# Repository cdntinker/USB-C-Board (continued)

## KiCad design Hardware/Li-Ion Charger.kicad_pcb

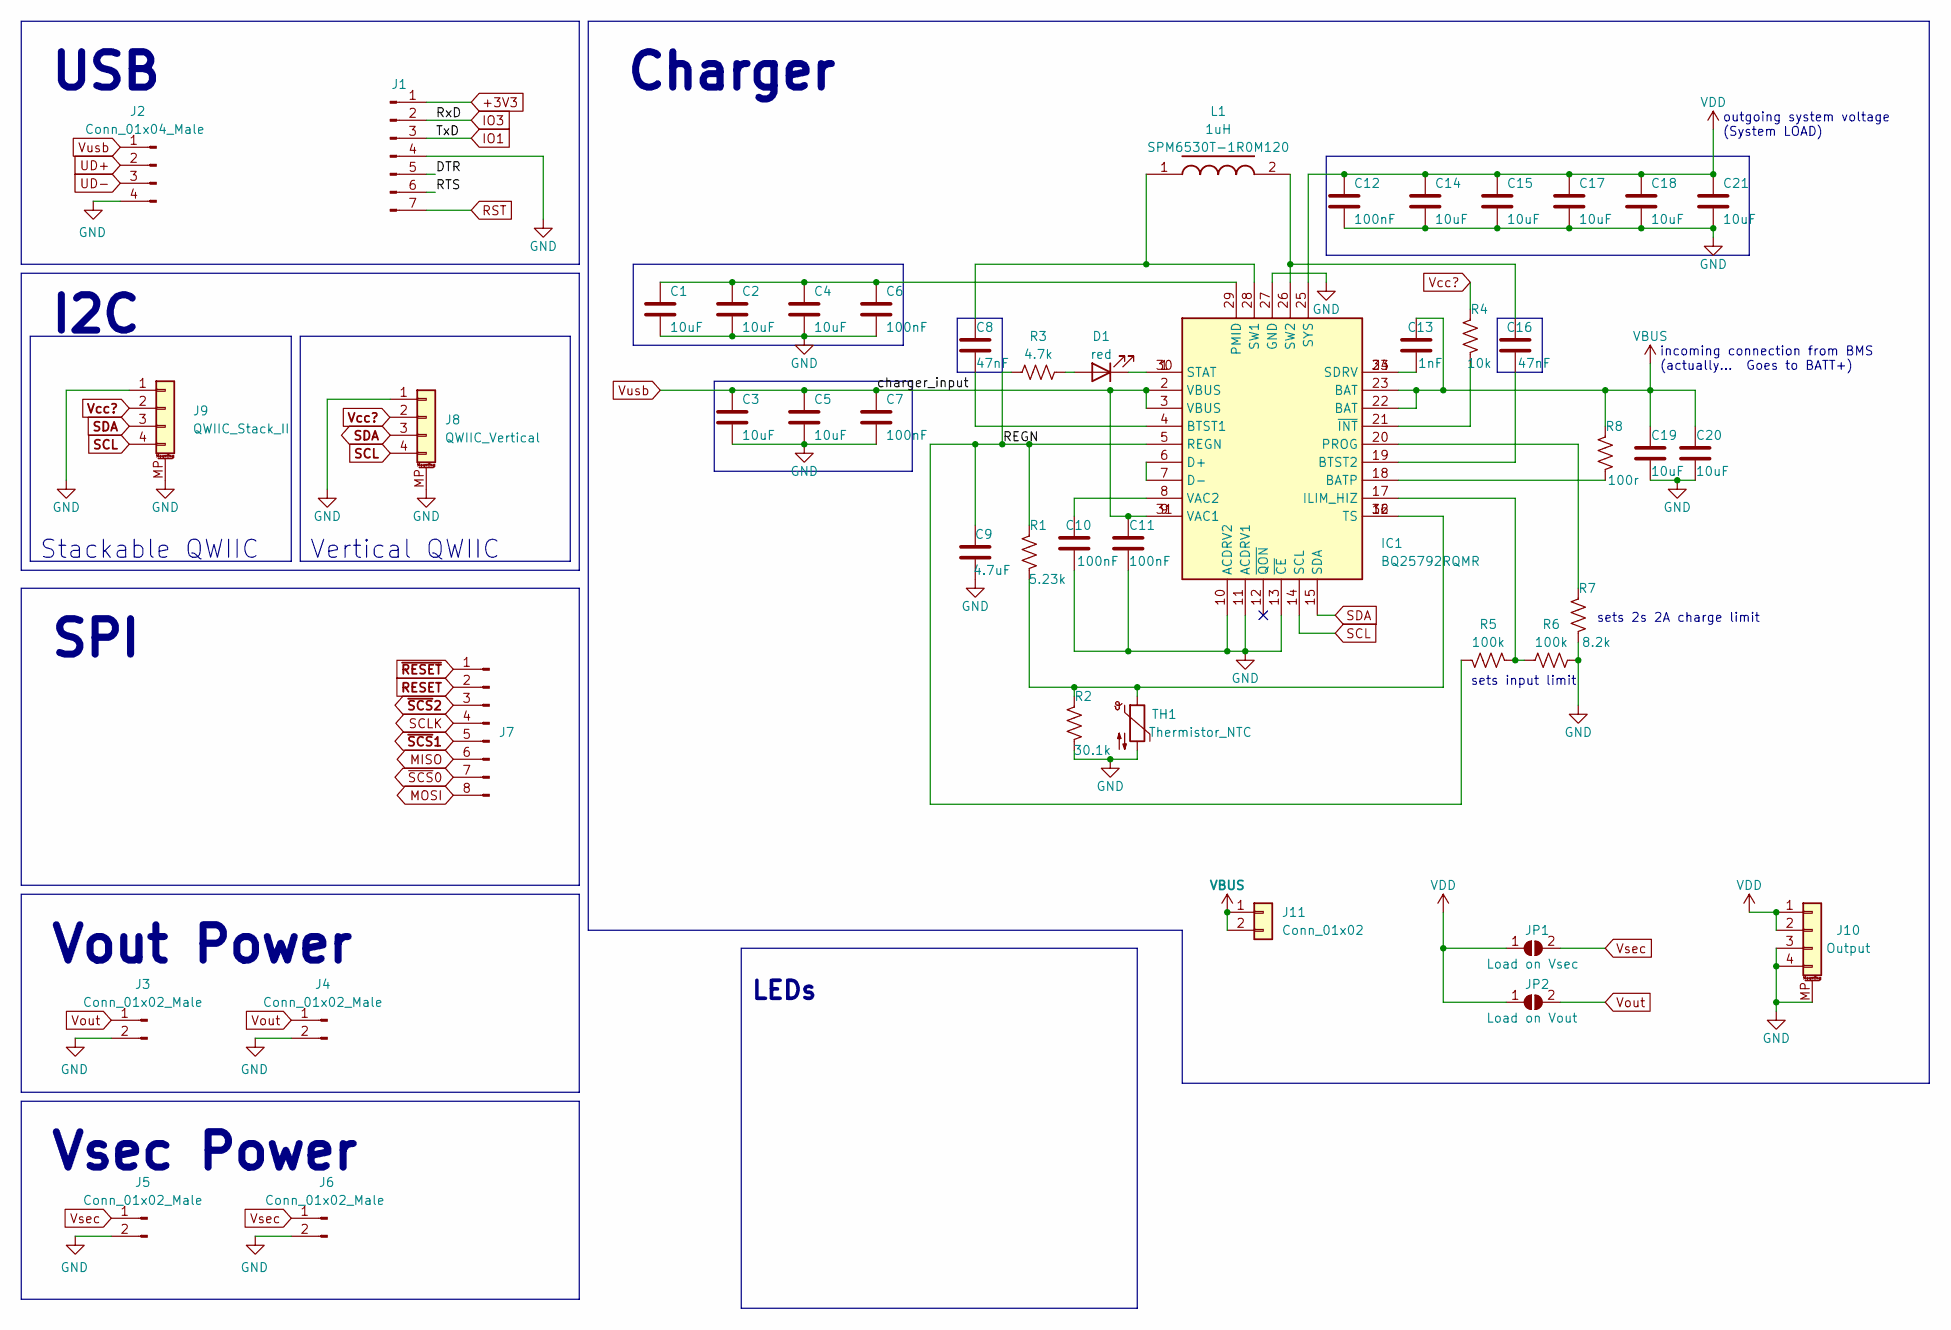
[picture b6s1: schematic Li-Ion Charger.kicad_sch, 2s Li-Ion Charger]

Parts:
C1, C2, C3, C4, C5, C14, C15, C17, C18, C19, C20, C21: 10uF; R_0603_1608Metric; LCSC C194427
C6, C7, C10, C11, C12: 100nF; R_0603_1608Metric
C8, C16: 47nF; R_0603_1608Metric; LCSC C469624
C9: 4.7uF; R_0603_1608Metric; LCSC C152930
C13: 1nF; R_0603_1608Metric
D1: red; LED_0603_1608Metric; LCSC C72038
IC1: BQ25792RQMR; Mouser 595-BQ25792RQMR
J1: Conn_01x07_Male; Board_Stacker_7
J2: Conn_01x04_Male; Board_Stacker_4; LCSC C2938401 + C2881513
J3, J4, J5, J6: Conn_01x02_Male; Board_Stacker_2; LCSC C2938400 + C2881511
J7: Conn_01x08_Male; PinHeader_2x04_P1.27mm_Vertical; LCSC C2881786 + C2684732
J8: QWIIC_Vertical; LCSC C145961
J9: QWIIC_Stack_II; LCSC C145956 + C2938401 + C2881513
J10: Output; JST_GH_SM04B-GHS-TB_1x04-1MP_P1.25mm_Horizontal; LCSC C225113
J11: Conn_01x02; PinSocket_1x02_P1.27mm_Vertical
JP1: Load on Vsec; SolderJumper-2_P_Open_Rounded_skinny
JP2: Load on Vout; SolderJumper-2_P_Open_Rounded_skinny
L1: 1uH; SPM6530_TDK; Mouser 810-SPM6530T-1R0M120
R1: 5.23k; R_0603_1608Metric
R2: 30.1k; R_0603_1608Metric; LCSC C2960871
R3: 4.7k; R_0603_1608Metric
R4: 10k; R_0603_1608Metric; LCSC C98220
R5, R6: 100k; R_0603_1608Metric
R7: 8.2k; R_0603_1608Metric
R8: 100r; R_0603_1608Metric
TH1: Thermistor_NTC; R_0603_1608Metric; LCSC C13564

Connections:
/REGN: C9.2, IC1.5 (REGN), R1.1, R3.1, R5.2
GND: C1.1, C2.1, C3.1, C4.1, C5.1, C6.1, C7.1, C9.1, C10.1, C11.1, C12.1, C14.1, C15.1, C17.1, C18.1, C19.1, C20.1, C21.1, IC1.10 (ACDRV2), IC1.11 (ACDRV1), IC1.13 (~CE), IC1.27 (GND), J1.4, J2.4, J3.2, J4.2, J5.2, J6.2, J8.1, J8.MP (MountPin), J9.1, J9.MP (MountPin), J10.3, J10.4, J10.MP (MountPin), R2.2, R6.2, R7.2, TH1.2
MISO: J7.6
MOSI: J7.8
unnamed: C1.2, C2.2, C4.2, C6.2, IC1.29 (PMID)
unnamed: C8.1, IC1.28 (SW1), L1.1
unnamed: C8.2, IC1.4 (BTST1)
unnamed: C10.2, IC1.8 (VAC2)
unnamed: C13.1, IC1.24 (SDRV), IC1.33 (SDRV)
unnamed: C16.1, IC1.19 (BTST2)
unnamed: C16.2, IC1.26 (SW2), L1.2
unnamed: D1.1 (K), IC1.1 (STAT), IC1.30 (STAT)
unnamed: D1.2 (A), R3.2
unnamed: IC1.6 (D+), IC1.7 (D-)
unnamed: IC1.16 (TS), IC1.32 (TS), R1.2, R2.1, TH1.1
unnamed: IC1.17 (ILIM_HIZ), R5.1, R6.1
unnamed: IC1.18 (BATP), R8.2
unnamed: IC1.20 (PROG), R7.1
unnamed: IC1.21 (~INT), R4.1
RESET: J7.2
SCL: IC1.14 (SCL), J8.4, J9.4
SCLK: J7.4
SDA: IC1.15 (SDA), J8.3, J9.3
UD+: J2.2
UD-: J2.3
VBUS: C13.2, C19.2, C20.2, IC1.22 (BAT), IC1.23 (BAT), J11.1, J11.2, R8.1
VDD: C12.2, C14.2, C15.2, C17.2, C18.2, C21.2, IC1.25 (SYS), J10.1, J10.2, JP1.1 (A), JP2.1 (A)
Vcc?: J8.2, J9.2, R4.2
Vout: J3.1, J4.1, JP2.2 (B)
Vsec: J5.1, J6.1, JP1.2 (B)
Vusb: C3.2, C5.2, C7.2, C11.2, IC1.2 (VBUS), IC1.3 (VBUS), IC1.9 (VAC1), IC1.31 (VAC1), J2.1
~RESET: J7.1
~SCS0: J7.7
~SCS1: J7.5
~SCS2: J7.3

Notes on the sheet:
Vout Power
I2C
Stackable QWIIC
incoming connection from BMS (actually... Goes to BATT+)
sets 2s 2A charge limit
SPI
Vsec Power
USB
outgoing system voltage (System LOAD)
sets input limit
Vertical QWIIC
Charger
LEDs

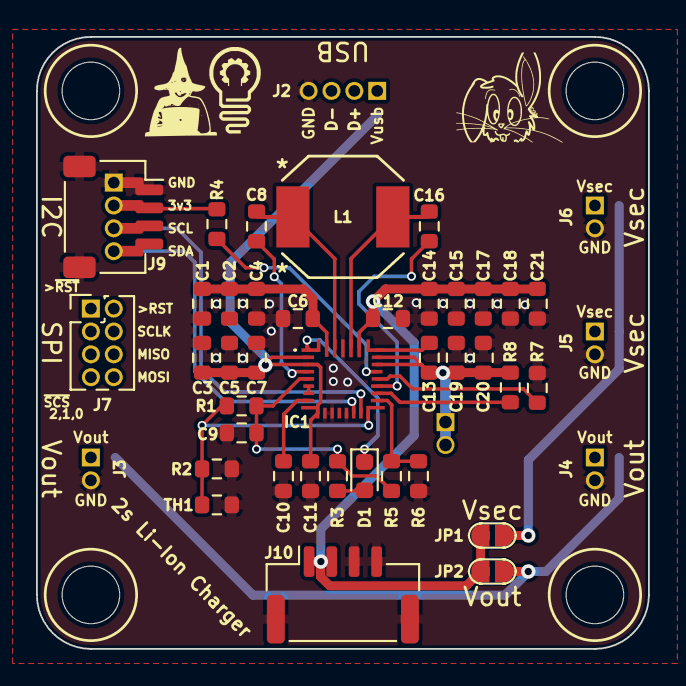
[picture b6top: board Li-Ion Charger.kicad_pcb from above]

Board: 2 copper layers, 34.0 x 34.0 mm, 44 parts (1 on the bottom side), 25 nets.

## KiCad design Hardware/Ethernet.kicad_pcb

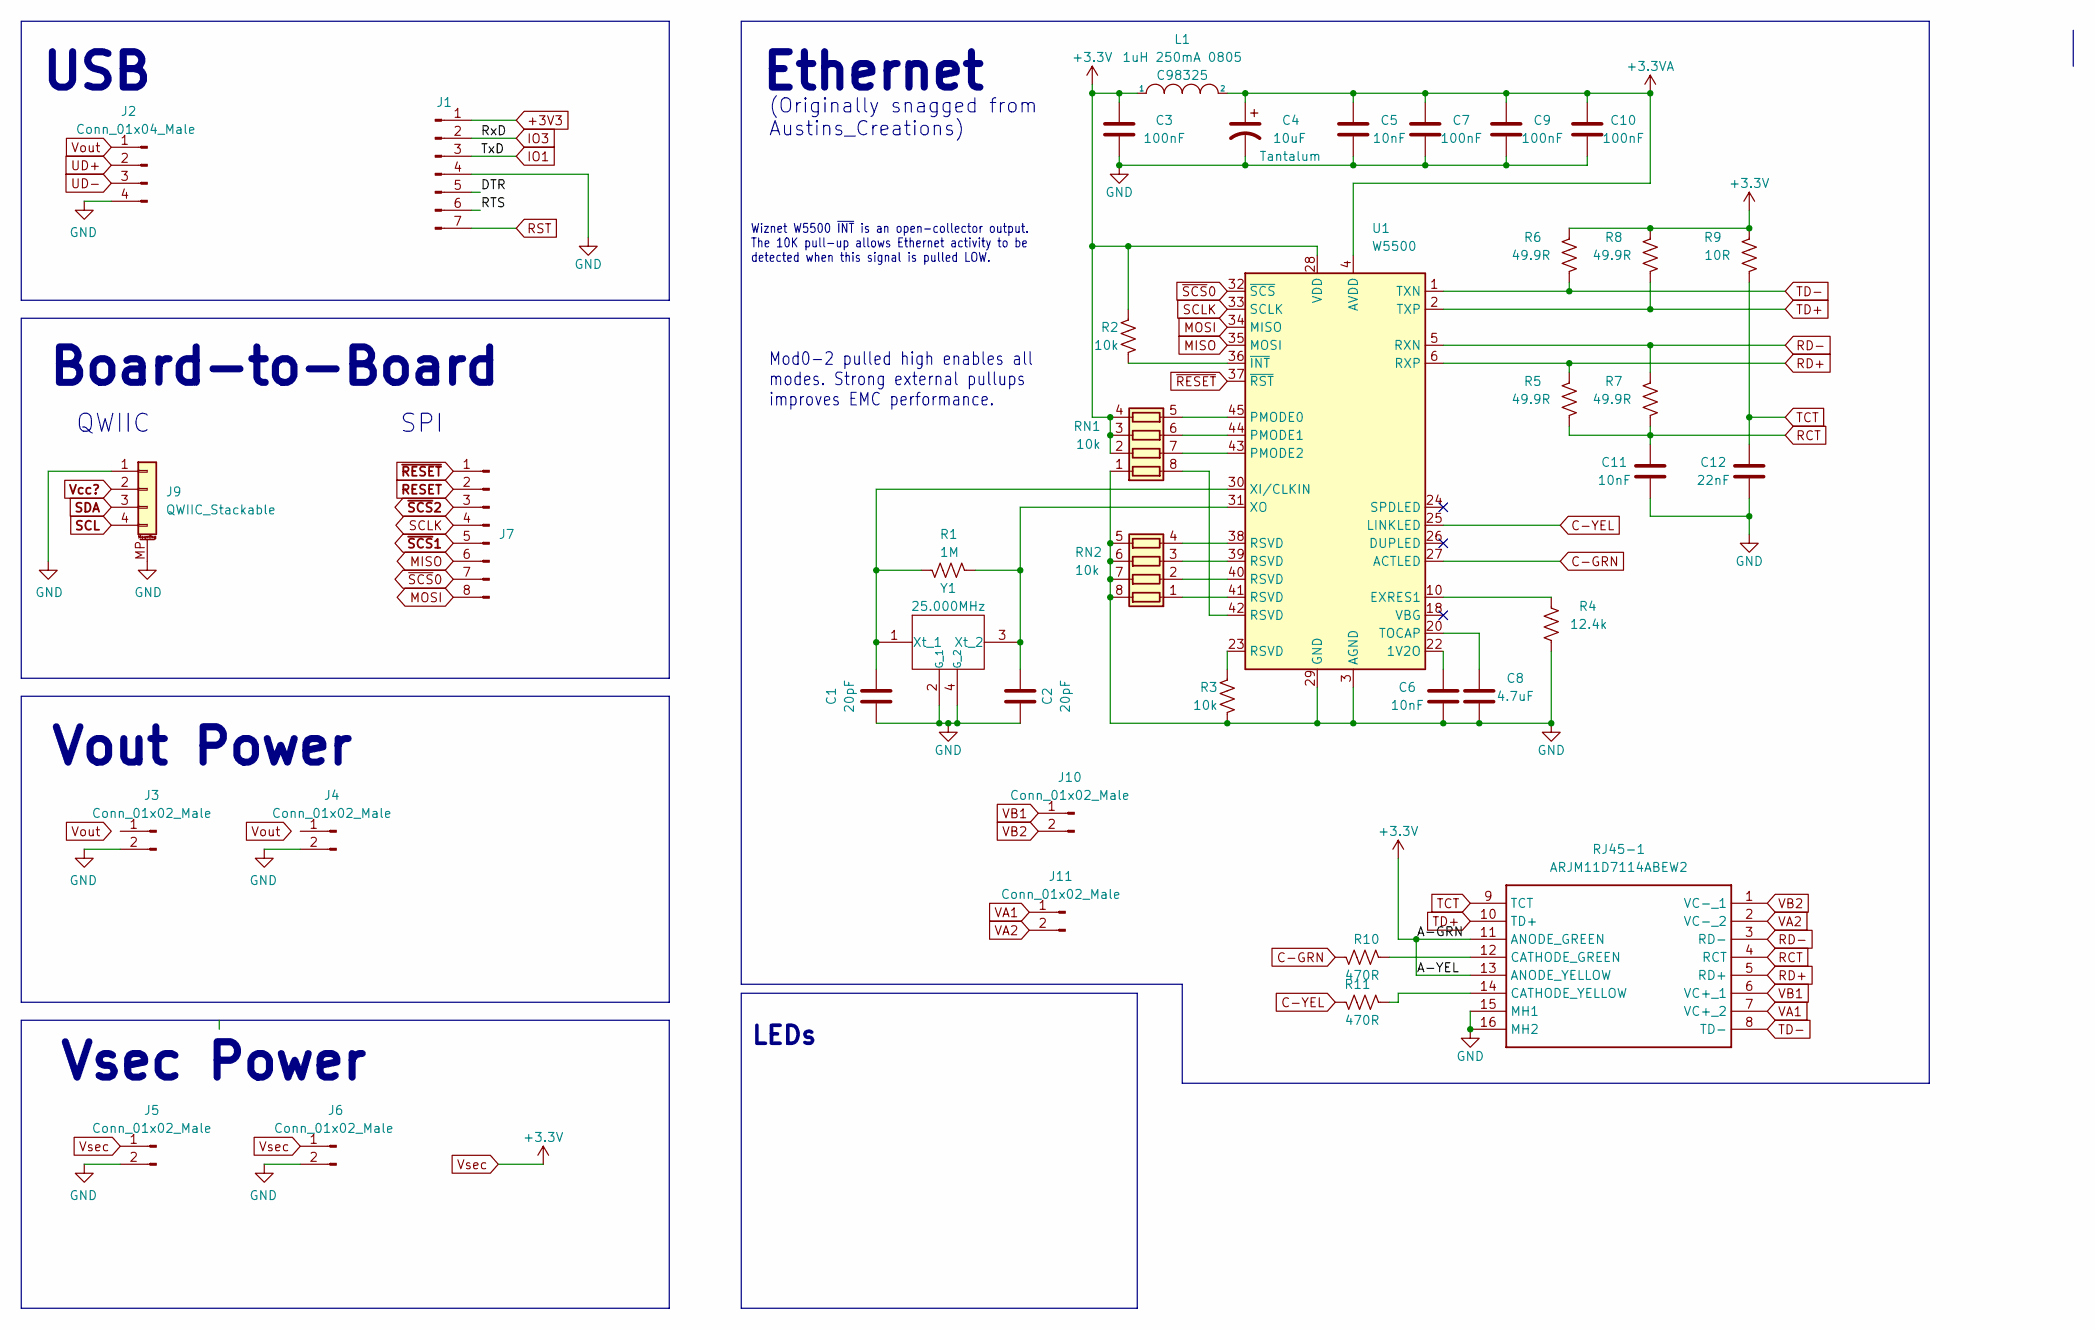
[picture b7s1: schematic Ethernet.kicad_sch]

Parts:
C1, C2: 20pF; C_0603_1608Metric; LCSC C105621
C3, C7, C9, C10: 100nF; C_0603_1608Metric; LCSC C14663
C4: 10uF; CP_EIA-3216-18_Kemet-A; LCSC C127946
C5, C6, C11: 10nF; C_0603_1608Metric; LCSC C57112
C8: 4.7uF; C_0603_1608Metric; LCSC C152930
C12: 22nF; C_0603_1608Metric; LCSC C302044
J1: Conn_01x07_Male; Board_Stacker_7
J2: Conn_01x04_Male; Board_Stacker_4
J3, J4, J5, J6: Conn_01x02_Male; Board_Stacker_2
J7: Conn_01x08_Male; PinHeader_2x04_P1.27mm_Vertical; LCSC C2881786 + C2684732
J9: QWIIC_Stackable; QWIIC_Stack_II
J10, J11: Conn_01x02_Male; PinSocket_1x02_P1.27mm_Vertical_SMD_Pin1Right
L1: 1uH 250mA 0805; L_0805_2012Metric; LCSC C98325
R1: 1M; R_0603_1608Metric; LCSC C328343
R2, R3: 10k; R_0603_1608Metric; LCSC C103199
R4: 12.4k; R_0603_1608Metric; LCSC C269455
R5, R6, R7, R8: 49.9R; R_0603_1608Metric; LCSC C103679
R9: 10R; R_0603_1608Metric; LCSC C103222
R10, R11: 470R; R_0603_1608Metric; LCSC C25241
RJ45-1: ARJM11D7114ABEW2; CONN_ARJM11D7-114-AB-EW2_ABR
RN1, RN2: 10k; R_Array_Convex_4x0603; LCSC C29718
U1: W5500; LQFP-48_7x7mm_P0.5mm; LCSC C32843
Y1: 25.000MHz; ABM825000MHz10B1UT; LCSC C258949

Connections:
+3.3VA: C4.1, C5.2, C7.2, C9.2, C10.2, L1.2, U1.4 (AVDD), U1.8 (AVDD), U1.11 (AVDD), U1.15 (AVDD), U1.17 (AVDD), U1.21 (AVDD)
C-GRN: R10.2, U1.27 (ACTLED)
C-YEL: R11.2, U1.25 (LINKLED)
GND: C1.1, C2.1, C3.1, C4.2, C5.1, C6.1, C7.1, C8.1, C9.1, C10.1, C11.1, C12.1, J1.4, J2.4, J3.2, J4.2, J5.2, J6.2, J9.1, J9.MP (MountPin), R3.1, R4.1, RJ45-1.15 (MH1), RJ45-1.16 (MH2), RN1.1 (R1.1), RN2.5 (R4.2), RN2.6 (R3.2), RN2.7 (R2.2), RN2.8 (R1.2), U1.3 (AGND), U1.9 (AGND), U1.14 (AGND), U1.16 (AGND), U1.19 (AGND), U1.29 (GND), U1.48 (AGND), Y1.2 (G_1), Y1.4 (G_2)
MISO: J7.6, U1.35 (MOSI)
MOSI: J7.8, U1.34 (MISO)
unnamed: C1.2, R1.1, U1.30 (XI/CLKIN), Y1.1 (Xt_1)
unnamed: C2.2, R1.2, U1.31 (XO), Y1.3 (Xt_2)
unnamed: C6.2, U1.22 (1V2O)
unnamed: C8.2, U1.20 (TOCAP)
unnamed: R2.1, U1.36 (~INT)
unnamed: R3.2, U1.23 (RSVD)
unnamed: R4.2, U1.10 (EXRES1)
unnamed: R10.1, RJ45-1.12 (CATHODE_GREEN)
unnamed: R11.1, RJ45-1.14 (CATHODE_YELLOW)
unnamed: RN1.5 (R4.2), U1.45 (PMODE0)
unnamed: RN1.6 (R3.2), U1.44 (PMODE1)
unnamed: RN1.7 (R2.2), U1.43 (PMODE2)
unnamed: RN1.8 (R1.2), U1.42 (RSVD)
unnamed: RN2.1 (R1.1), U1.41 (RSVD)
unnamed: RN2.2 (R2.1), U1.40 (RSVD)
unnamed: RN2.3 (R3.1), U1.39 (RSVD)
unnamed: RN2.4 (R4.1), U1.38 (RSVD)
RCT: C11.2, R5.1, R7.1, RJ45-1.4 (RCT)
RD+: R5.2, RJ45-1.5 (RD+), U1.6 (RXP)
RD-: R7.2, RJ45-1.3 (RD-), U1.5 (RXN)
RESET: J7.2
SCL: J9.4
SCLK: J7.4, U1.33 (SCLK)
SDA: J9.3
TCT: C12.2, R9.1, RJ45-1.9 (TCT)
TD+: R8.1, RJ45-1.10 (TD+), U1.2 (TXP)
TD-: R6.1, RJ45-1.8 (TD-), U1.1 (TXN)
VA1: J11.1, RJ45-1.7 (VC+_2)
VA2: J11.2, RJ45-1.2 (VC-_2)
VB1: J10.1, RJ45-1.6 (VC+_1)
VB2: J10.2, RJ45-1.1 (VC-_1)
Vcc?: J9.2
Vsec: C3.2, J5.1, J6.1, L1.1, R2.2, R6.2, R8.2, R9.2, RJ45-1.11 (ANODE_GREEN), RJ45-1.13 (ANODE_YELLOW), RN1.2 (R2.1), RN1.3 (R3.1), RN1.4 (R4.1), U1.28 (VDD)
~RESET: J7.1, U1.37 (~RST)
~SCS0: J7.7, U1.32 (~SCS)
~SCS1: J7.5
~SCS2: J7.3

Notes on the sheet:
Vsec Power
Vout Power
QWIIC
Wiznet W5500 ~{INT} is an open-collector output. The 10K pull-up allows Ethernet activity to be detected when this signal is pulled LOW.
USB
Board-to-Board
Mod0-2 pulled high enables all modes. Strong external pullups improves EMC performance.
(Originally snagged from Austins_Creations)
SPI
Ethernet
LEDs

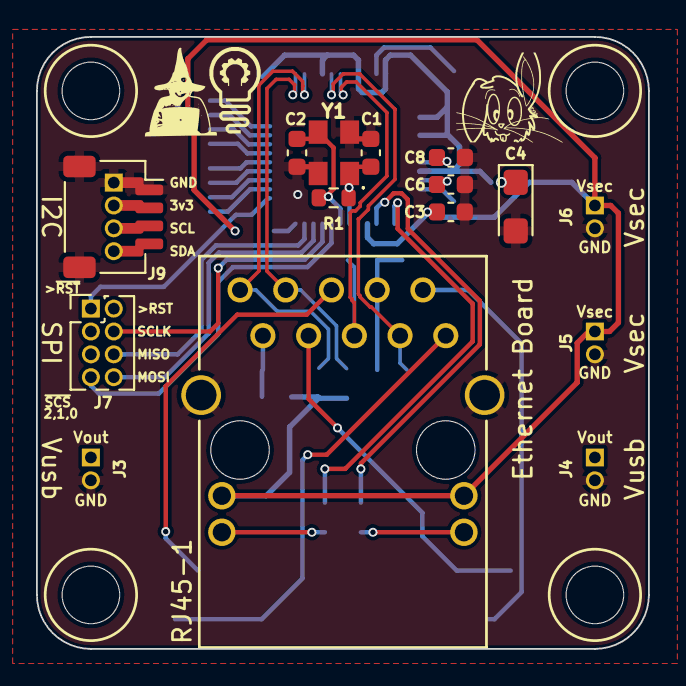
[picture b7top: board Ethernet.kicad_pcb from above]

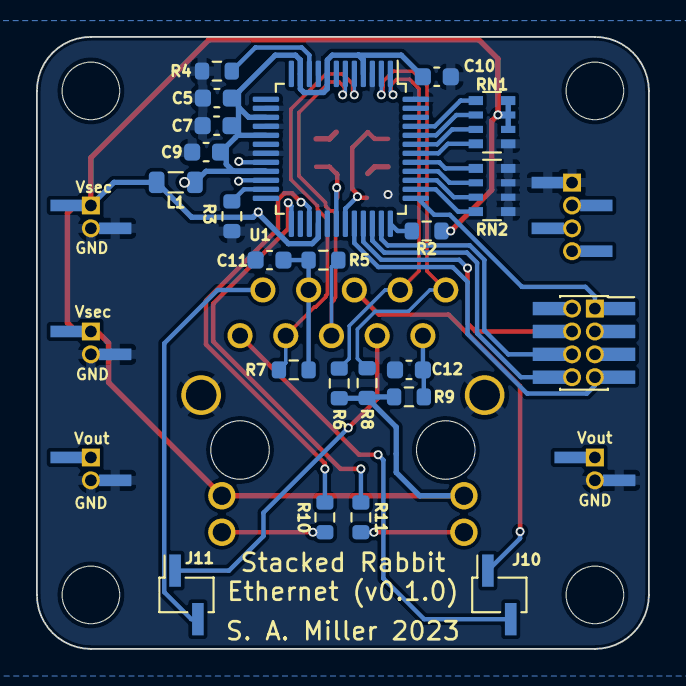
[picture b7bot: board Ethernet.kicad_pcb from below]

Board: 2 copper layers, 34.0 x 34.0 mm, 37 parts (22 on the bottom side), 37 nets.

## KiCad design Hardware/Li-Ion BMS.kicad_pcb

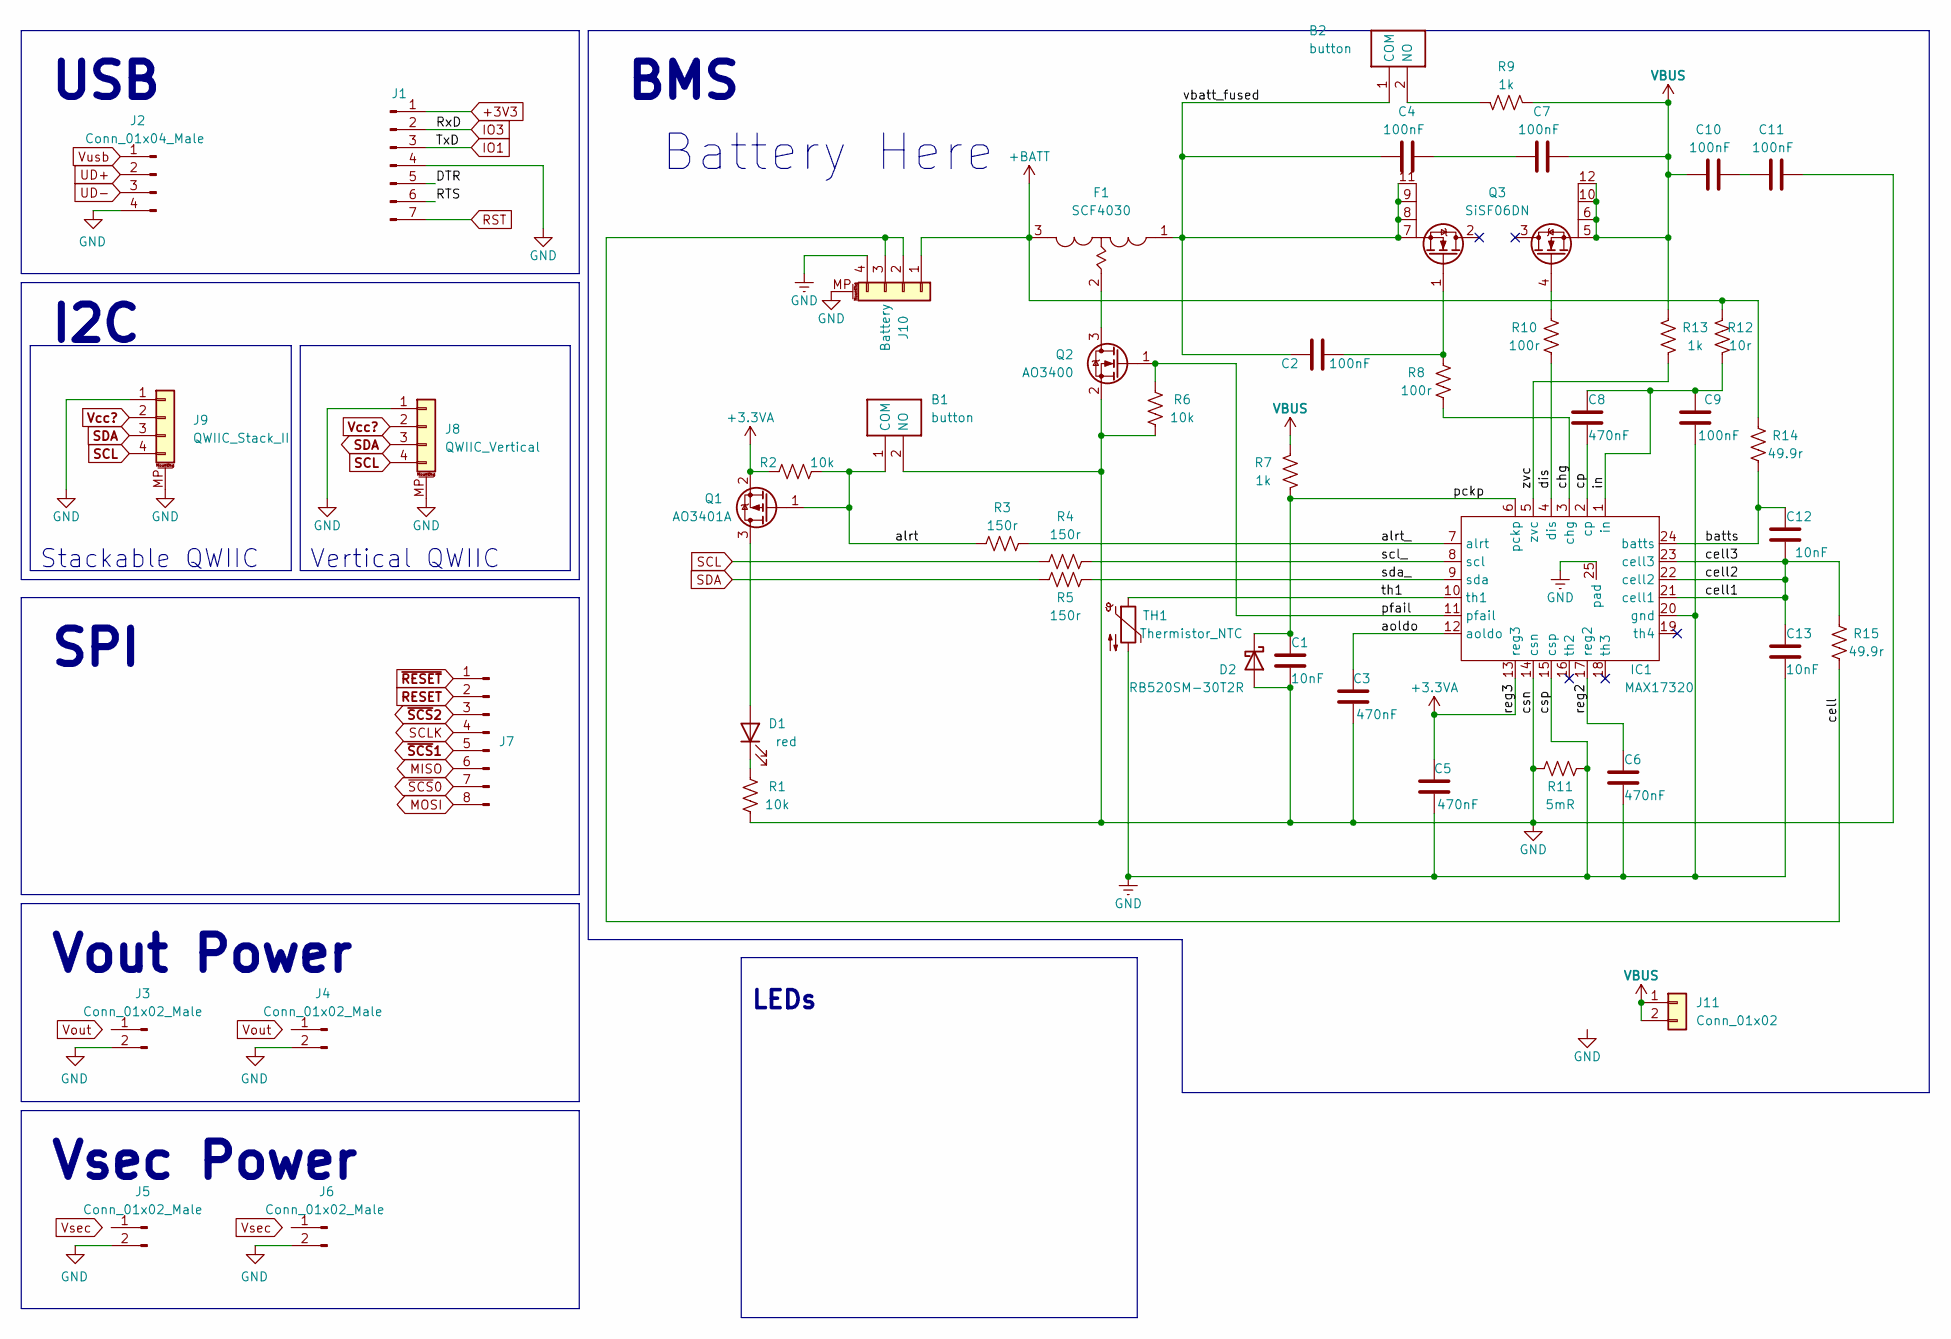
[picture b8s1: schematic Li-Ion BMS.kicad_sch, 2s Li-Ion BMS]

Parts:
B1, B2: button; SW_Push_TS273014TP; LCSC C410373
C1, C12, C13: 10nF; R_0603_1608Metric; LCSC C107059
C2: 100nF; R_0603_1608Metric
C3, C5, C6, C8: 470nF; R_0603_1608Metric; LCSC C1704
C4, C7, C9, C10, C11: 100nF; R_0603_1608Metric; LCSC C83060
D1: red; LED_0603_1608Metric; LCSC C72038
D2: RB520SM-30T2R; D_SOD-523; LCSC C123011
F1: SCF4030; SCF40301204; mouser 504-SCF4030-12-05
IC1: MAX17320; QFN-24-1EP_4x4mm_P0.5mm_EP2.6x2.6mm; mouser 700-MAX17320G20+T
J1: Conn_01x07_Male; Board_Stacker_7
J2: Conn_01x04_Male; Board_Stacker_4; LCSC C2938401 + C2881513
J3, J4, J5, J6: Conn_01x02_Male; Board_Stacker_2; LCSC C2938400 + C2881511
J7: Conn_01x08_Male; PinHeader_2x04_P1.27mm_Vertical; LCSC C2881786 + C2684732
J8: QWIIC_Vertical; LCSC C145961
J9: QWIIC_Stack_II; LCSC C145956 + C2938401 + C2881513
J10: Battery; JST_GH_SM04B-GHS-TB_1x04-1MP_P1.25mm_Horizontal; LCSC C225113
J11: Conn_01x02; PinHeader_1x02_P1.27mm_Vertical
Q1: AO3401A; SOT-23; LCSC C347476
Q2: AO3400; SOT-23; LCSC C20917
Q3: SiSF06DN; SISF06DNT1GE3; mouser 78-SISF06DN-T1-GE3
R1, R2, R6: 10k; R_0603_1608Metric; LCSC C98220
R3, R4, R5: 150r; R_0603_1608Metric; LCSC C22808
R7, R9, R13: 1k; R_0603_1608Metric; LCSC C21190
R8, R10: 100r; R_0603_1608Metric; LCSC C22775
R11: 5mR; R_2512_6332Metric; LCSC C1021512
R12: 10r; R_0603_1608Metric; LCSC C22859
R14, R15: 49.9r; R_0603_1608Metric; LCSC C103679
TH1: Thermistor_NTC; R_0603_1608Metric; LCSC C13564

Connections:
+3.3VA: C5.1, IC1.13 (reg3), Q1.2 (S), R2.1
+BATT: F1.3, J10.1, R12.1, R14.1
/alrt: B1.1 (COM), Q1.1 (G), R2.2, R3.1
/alrt_: IC1.7 (alrt), R3.2
/aoldo: C3.1, IC1.12 (aoldo)
/batts: C12.1, IC1.24 (batts), R14.2
/cell: J10.2, J10.3, R15.2
/cell1: C12.2, C13.1, IC1.21 (cell1), IC1.22 (cell2), IC1.23 (cell3), R15.1
/chg: IC1.3 (chg), R8.1
/cp: C8.2, IC1.2 (cp)
/dis: IC1.4 (dis), R10.1
/in: C8.1, C9.1, IC1.1 (in), R12.2
/pckp: C1.2, D2.1 (K), IC1.6 (pckp), R7.2
/pfail: IC1.11 (pfail), Q2.1 (G), R6.1
/reg2: C6.1, IC1.17 (reg2)
/scl_: IC1.8 (scl), R4.2
/sda_: IC1.9 (sda), R5.1
/th1: IC1.10 (th1), TH1.1
/vbatt_fused: B2.1 (COM), C2.1, C4.1, F1.1, Q3.7 (S1), Q3.8 (S1), Q3.9 (S1), Q3.11 (S1)
/zvc: IC1.5 (zvc), R13.1
MISO: J7.6
MOSI: J7.8
unnamed: B2.2 (NO), R9.2
unnamed: C2.2, Q3.1 (G1), R8.2
unnamed: C4.2, C7.1
unnamed: C10.2, C11.1
unnamed: D1.1 (K), R1.1
unnamed: D1.2 (A), Q1.3 (D)
unnamed: F1.2, Q2.3 (D)
unnamed: Q3.4 (G2), R10.2
RESET: J7.2
SCL: J8.4, J9.4, R4.1
SCLK: J7.4
SDA: J8.3, J9.3, R5.2
UD+: J2.2
UD-: J2.3
VBUS: C7.2, C10.1, J11.1, J11.2, Q3.5 (S2), Q3.6 (S2), Q3.10 (S2), Q3.12 (S2), R7.1, R9.1, R13.2
Vcc?: J8.2, J9.2
Vusb: J2.1
~RESET: J7.1
~SCS0: J7.7
~SCS1: J7.5
~SCS2: J7.3

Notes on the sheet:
Vout Power
I2C
Stackable QWIIC
SPI
Vsec Power
USB
Battery Here
Vertical QWIIC
BMS
LEDs

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
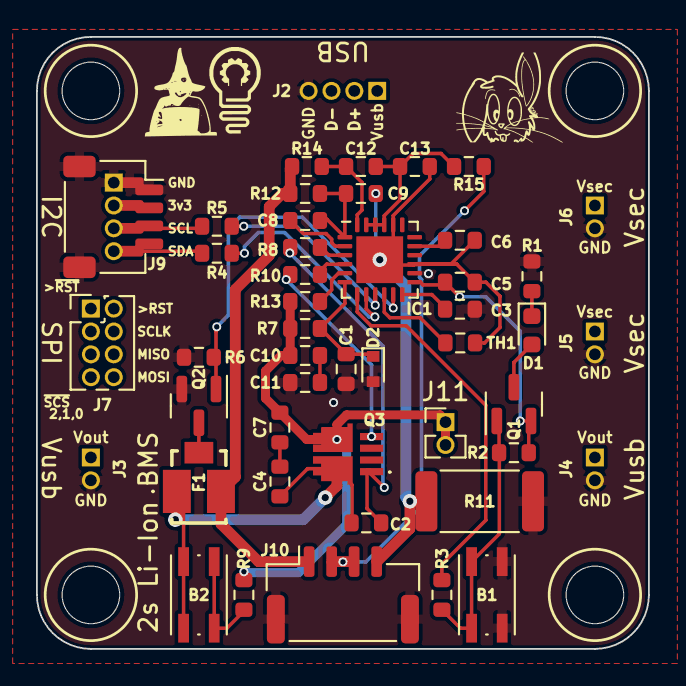
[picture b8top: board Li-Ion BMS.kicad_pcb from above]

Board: 2 copper layers, 34.0 x 34.0 mm, 47 parts (0 on the bottom side), 33 nets.

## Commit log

2023-09-06 added datasheets
2023-09-06 tweakin' header positions
2023-09-06 footprint tweaks...
2023-09-06 s'more tweakin'
2023-09-06 Added empty controller board
2023-09-07 starting on controller boards
2023-09-07 couple of 3D views
2023-09-10 fiddlin' with stuff...
2023-09-11 BOMing the place...
2023-09-11 Tryin' a 8285 controller...
2023-09-11 oof!
2023-09-11 added 8285 MCU board to 3D
2023-09-11 Mwahahaha
2023-09-12 Makin' WiFi an option...
2023-09-12 continuin' WiFi option...
2023-09-13 Improved QWIIC Stack + new LOGO
2023-09-14 tweakin' not twerkin
2023-09-14 :vomit:
2023-09-16 Nearly there...
2023-09-17 buncha tweaks...
2023-09-17 just fiddlin' 'round...
2023-09-17 Some cleanup
2023-09-17 Werkin' on READMEs
2023-09-17 moar cleanup
2023-09-18 tweaks...
2023-09-18 hehehe
2023-09-18 README updates
2023-09-18 messin' with the controller board
2023-09-18 aaarrrggg... RABBITS! Now there's a programmer board.
2023-09-18 Oh look... Pix!
2023-09-19 Cleaned up design of the Programmer board
2023-09-19 updated 3D models
2023-09-19 updated Pix
2023-09-19 Documentation...
2023-09-19 Documentation
2023-09-20 3D & Pix updates...
2023-09-20 Tinkerin' + RESET & LED on Programmer...
2023-09-21 Programmer Board Indicators!
2023-09-21 programmer 3D & Pix updates
2023-09-21 possibly, maybe, finalised Programmer Board?
2023-09-22 Expanding on the Controller Board functionality...
2023-09-22 Rabbit-Hole OCD... Redesigned Controller Board
2023-09-23 Much tweaking of Controller Board
2023-09-23 Some documentation updates
2023-09-24 Rabbit OCD attack...
2023-09-24 playin' about with the 3D renders...
2023-09-24 Moar playin' about with the 3D renders...
2023-09-27 Uber Rework!
2023-09-29 Redesignating repo "The NerdMage Rabbit Stack".
2023-09-29 Working on SPI
2023-09-29 Refining the Ethernet board
2023-09-29 future rabbit holes...
2023-09-30 Buncha cosmetic stuff...
2023-09-30 Starting on POE
2023-09-30 Playin' around with the 3D rendering stuff...
2023-09-30 More on POE...
2023-10-01 Some randomness...
2023-10-01 Adding an RP2040 board...
2023-10-02 Tarduino!!!!!!!!!!!!!!!!!!!!!
2023-10-02 whole bunche cleanup...
2023-10-02 more random cleanup...
2023-10-03 a little bit more cleanup...
2023-10-03 Making J7 I2C + SPI only...
2023-10-03 Still cleaning up J7
2023-10-03 still messing about with SPI stuff...
2023-10-04 more cleanup...
2023-10-05 PD Board rework for J7 & J9
2023-10-05 Cleanup & working on J7/J9 rework
2023-10-06 Working on changes to J7/J9
2023-10-06 Still working on changes to J7/J9
2023-10-06 Still working on changes to J7/J9...
2023-10-07 Still migrating to 0.2.x
2023-10-08 Re-doing Random VREG
2023-10-08 Random VREG!
2023-10-08 Ditching the "Early Designs" folder
2023-10-09 Bit more of the RP2040...
2023-10-09 I2C on the RP2040
2023-10-09 Working on Controller-Tarduino Clone
2023-10-10 Updated POE Board for J7/J9
2023-10-10 J7/J9 updates complete...
2023-10-10 updating Pix
2023-10-10 Some tweaks
2023-10-12 Working on the RP2040 & cleaning up stuff...
2023-10-14 Whole bunch of cleanup & 3D rework
2023-10-16 3D updates and a USB hub
2023-10-16 workin' on the USB Hub
2023-10-16 updates to 3D
2023-10-16 Updates to Pix
2023-10-17 added a handful of stackup examples
2023-10-19 And now... Battery Handling! Lithium Charger
2023-10-19 Now...There's a BMS for the Charger!
2023-10-22 Some updates to the hub
2023-10-24 Possibly completed USB Hub board
2023-10-24 USB Hub2... Now with Overcurrent Protection
2023-10-24 More about the Hub...
2023-10-24 Still... USB Hub...
2023-10-25 USB Hub2 is pretty much complete!
2023-10-25 Yay fer Hub2!
2023-10-29 s'more work on the hub
2024-03-01 Re-arranging the hardware files for better clarity.
